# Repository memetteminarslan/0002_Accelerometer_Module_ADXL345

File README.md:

# 0002_Accelerometer_Module_ADXL345
You are seeing a large number of widely used Accelerometer modules in electronic development kits. More information coming soon...

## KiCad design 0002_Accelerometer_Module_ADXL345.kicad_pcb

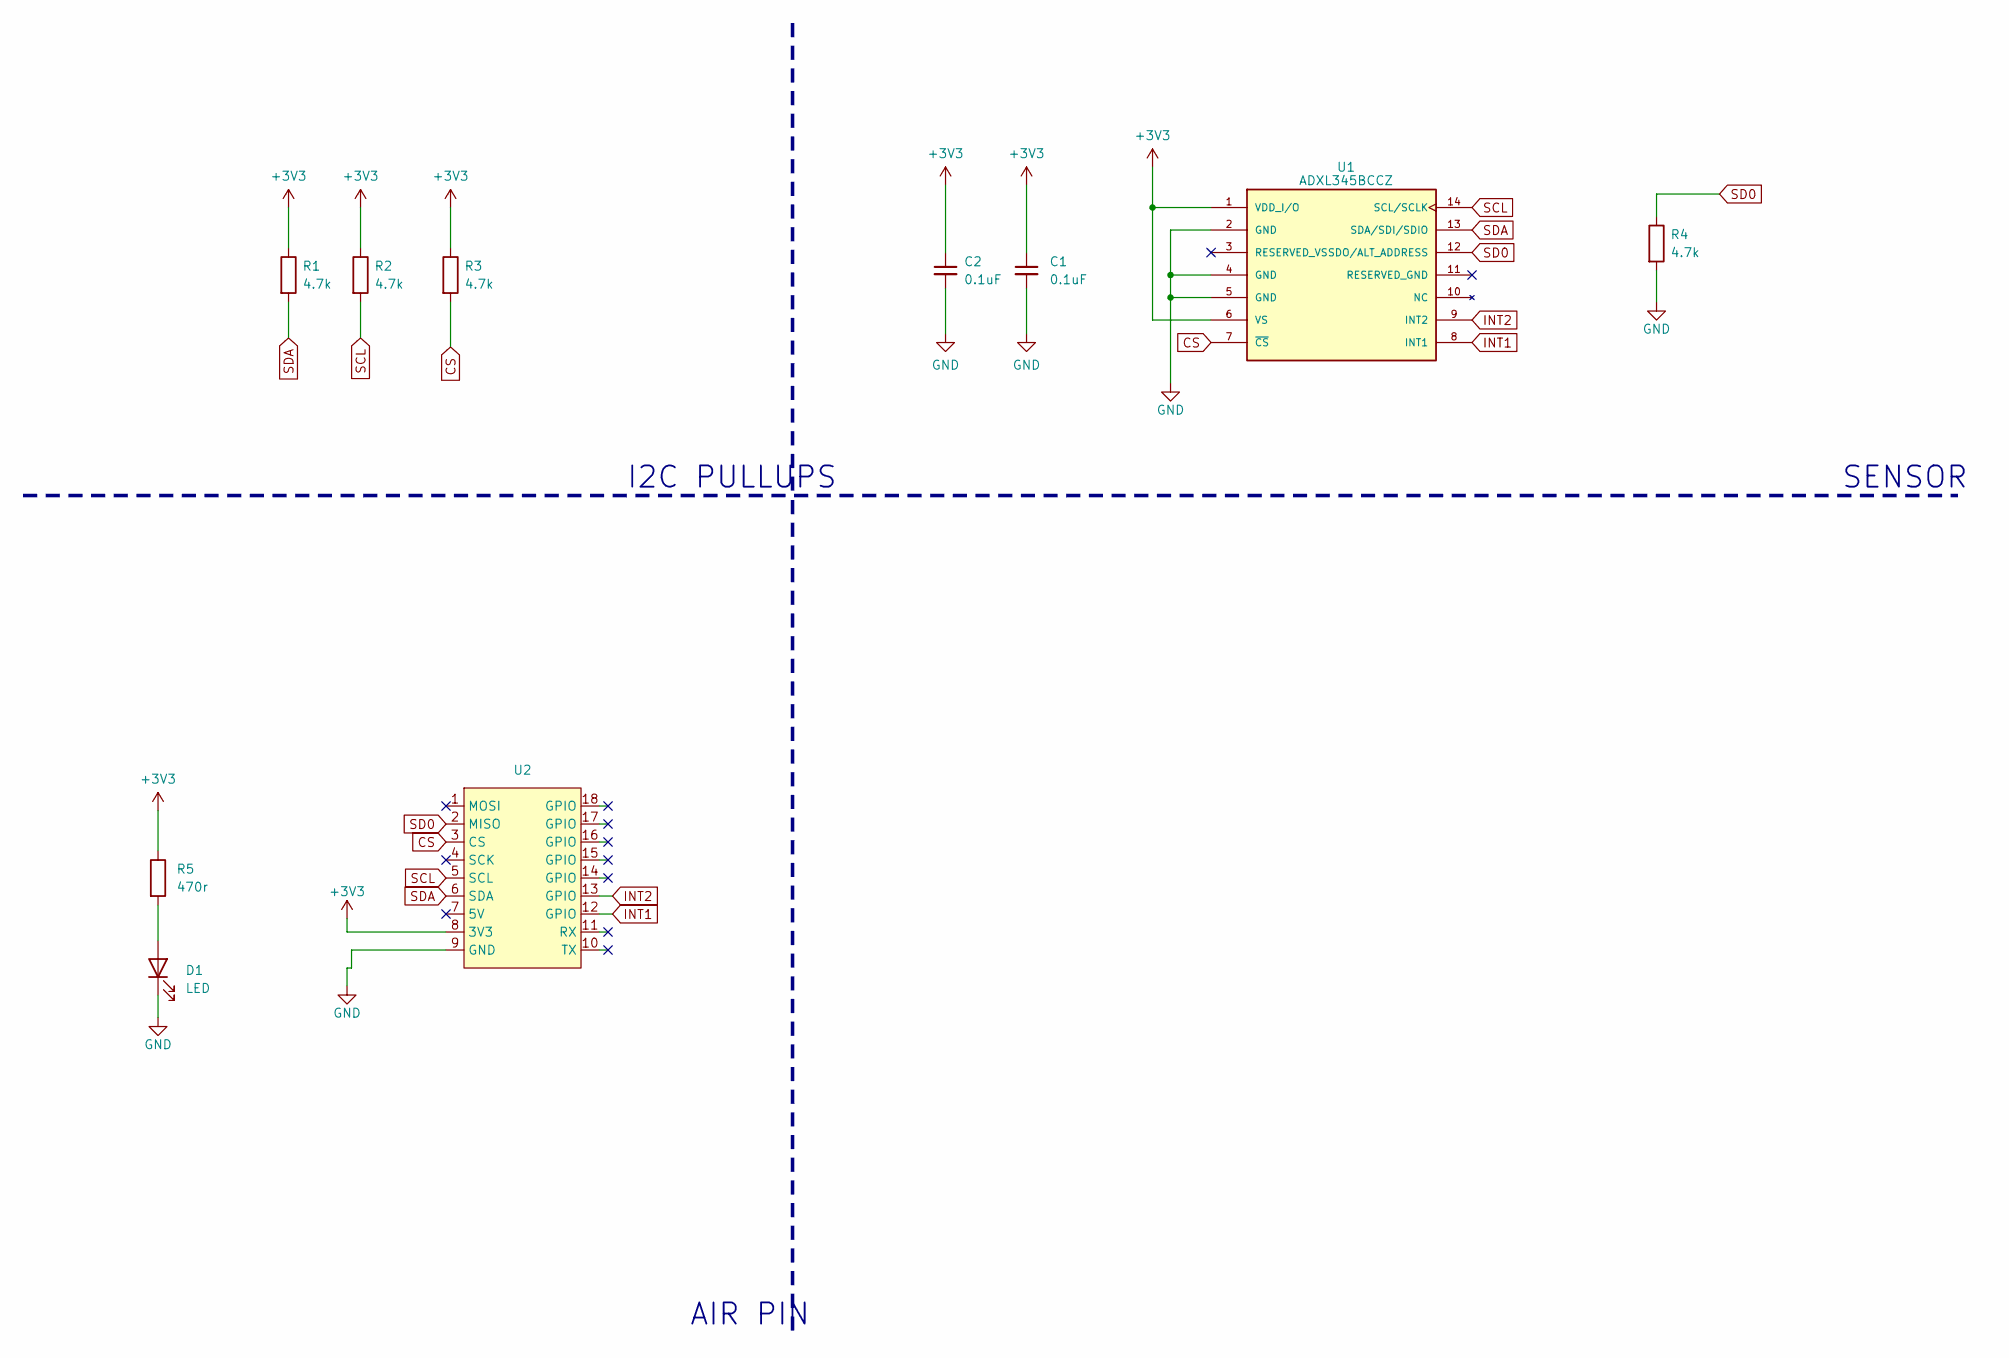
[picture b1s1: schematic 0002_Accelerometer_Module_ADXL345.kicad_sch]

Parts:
C1, C2: 0.1uF; C_0805_2012Metric
D1: LED; LED_0805_2012Metric
R1, R2, R3, R4: 4.7k; R_0805_2012Metric
R5: 470r; R_0805_2012Metric
U1: ADXL345BCCZ; IC_ADXL345BCCZ; PARTREV G
U2: air_module

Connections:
+3V3: C1.1, C2.1, R1.1, R2.1, R3.1, R5.1, U1.1 (VDD_I/O), U1.6 (VS), U2.8 (3V3)
CS: R3.2, U1.7 (~CS), U2.3 (CS)
GND: C1.2, C2.2, D1.1 (K), R4.2, U1.2 (GND), U1.4 (GND), U1.5 (GND), U2.9 (GND)
INT1: U1.8 (INT1), U2.12 (GPIO)
INT2: U1.9 (INT2), U2.13 (GPIO)
unnamed: D1.2 (A), R5.2
SCL: R2.2, U1.14 (SCL/SCLK), U2.5 (SCL)
SD0: R4.1, U1.12 (SDO/ALT_ADDRESS), U2.2 (MISO)
SDA: R1.2, U1.13 (SDA/SDI/SDIO), U2.6 (SDA)

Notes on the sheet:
I2C PULLUPS
AIR PIN
SENSOR

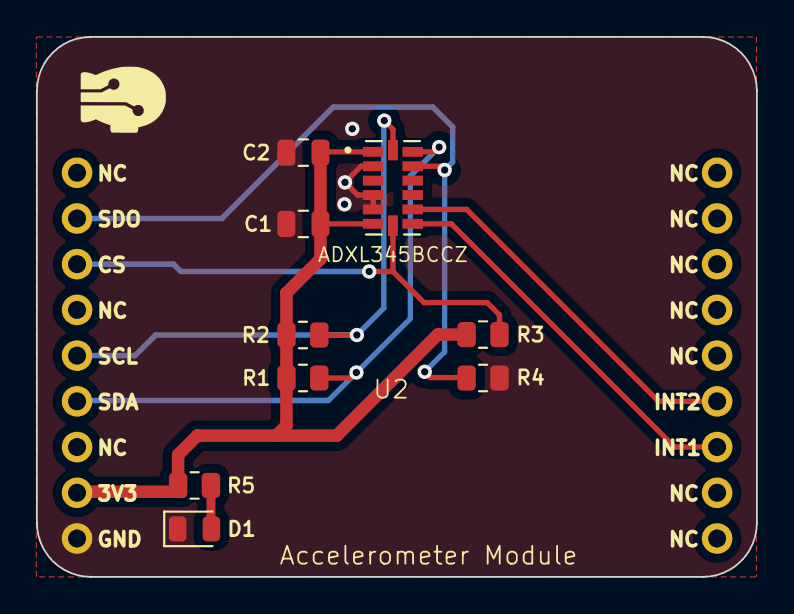
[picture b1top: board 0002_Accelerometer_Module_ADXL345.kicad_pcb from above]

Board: 2 copper layers, 40.0 x 30.0 mm, 10 parts (0 on the bottom side), 9 nets.
